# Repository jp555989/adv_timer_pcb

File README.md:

# adv_timer_pcb

This is a small project I made for one of my academic courses, I picked a task involving conversion from a THT based PCB to SMT based PCB, for the board I used in conversion I picked
an advanced impulse timer, the THT board can be seen here:
https://ep.com.pl/projekty/projekty-ep/15648-zaawansowany-licznik-impulsow

I didn't change mounting technology of components like microcontroller for the sake of comfort since it'd be easier to dismount it in case of any issues or to reprogram it.

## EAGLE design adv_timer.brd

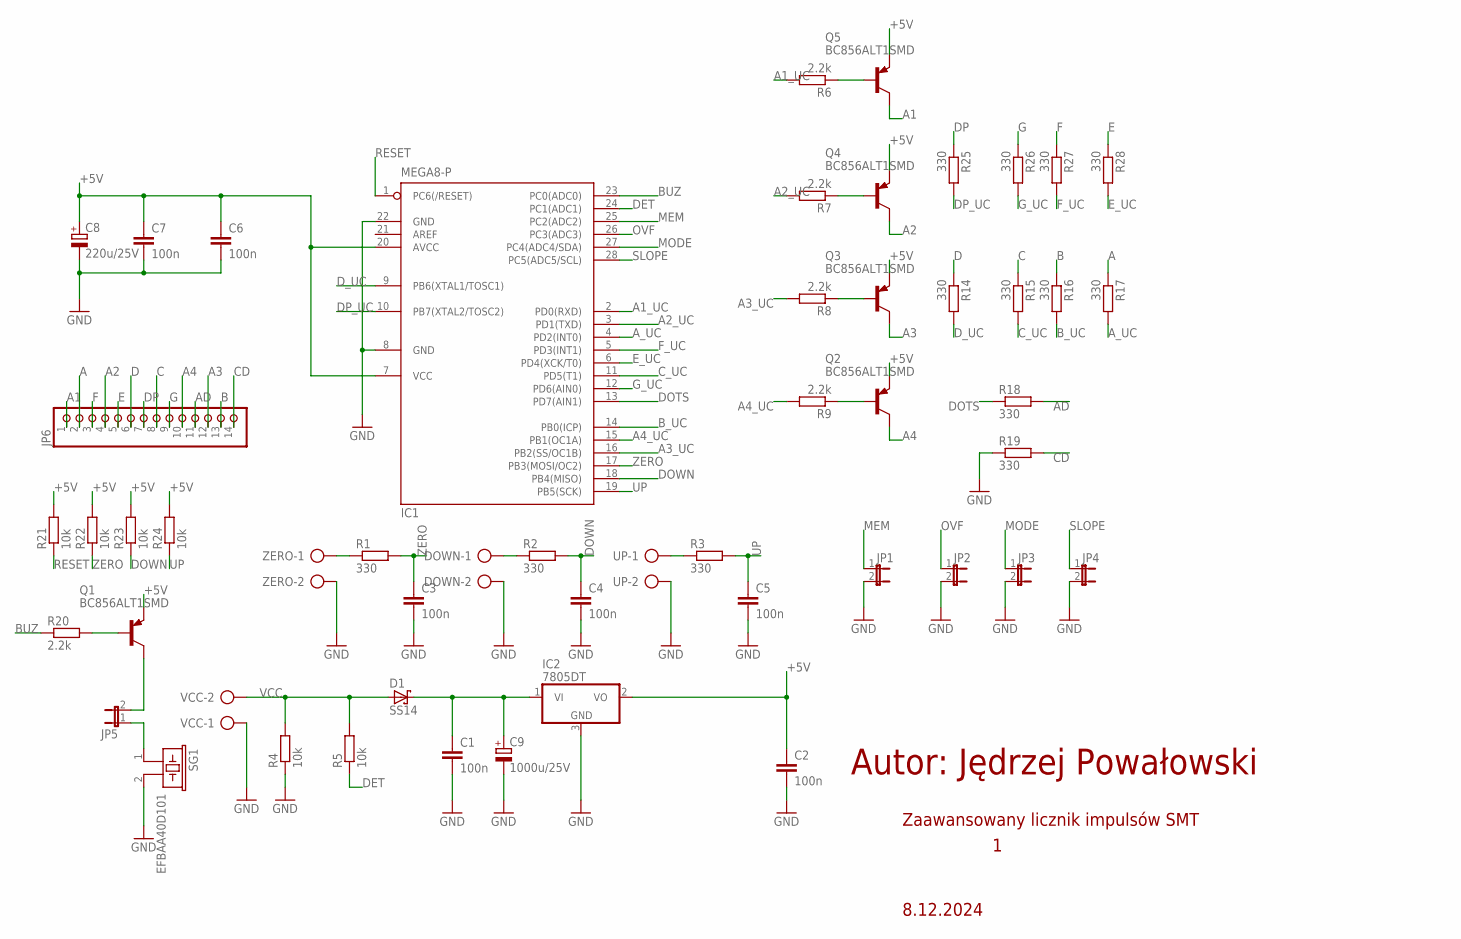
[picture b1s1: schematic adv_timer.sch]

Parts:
C1, C2, C3, C4, C5, C6, C7: 100n; C1210K
C8: 220u/25V; 153CLV-0810
C9: 1000u/25V; 153CLV-0810
D1: SS14; DO-214AC
DOWN: AK300/2
IC1: MEGA8-P; DIL28-3
IC2: 7805DT; TO252
JP1, JP2, JP3, JP4, JP5: JP1E; JP1
JP6: PINHD-1X14/90; 1X14/90
Q1, Q2, Q3, Q4, Q5: BC856ALT1SMD; SOT23-BEC
R1, R2, R3: 330; M1206
R4, R5: 10k; M1206
R6, R7, R8, R9, R20: 2.2k; R0805
R14, R15, R16, R17, R18, R19, R25, R26, R27, R28: 330; R0805
R21, R22, R23, R24: 10k; R0805
SG1: EFBAA40D101
UP: AK300/2
VCC: AK300/2
ZERO: AK300/2

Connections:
+5V: C2.1, C6.1, C7.1, C8.+, IC1.7 (VCC), IC1.20 (AVCC), IC2.2 (VO), Q1.E, Q2.E, Q3.E, Q4.E, Q5.E, R21.2, R22.2, R23.2, R24.2
A: JP6.2, R17.1
A1: JP6.1, Q5.C
A1_UC: IC1.2 (PD0(RXD)), R6.2
A2: JP6.4, Q4.C
A2_UC: IC1.3 (PD1(TXD)), R7.2
A3: JP6.12, Q3.C
A3_UC: IC1.16 (PB2(SS/OC1B)), R8.2
A4: JP6.10, Q2.C
A4_UC: IC1.15 (PB1(OC1A)), R9.2
AD: JP6.11, R18.2
A_UC: IC1.4 (PD2(INT0)), R17.2
B: JP6.13, R16.1
BUZ: IC1.23 (PC0(ADC0)), R20.1
B_UC: IC1.14 (PB0(ICP)), R16.2
C: JP6.8, R15.1
CD: JP6.14, R19.2
C_UC: IC1.11 (PD5(T1)), R15.2
D: JP6.6, R14.1
DET: IC1.24 (PC1(ADC1)), R5.1
DOTS: IC1.13 (PD7(AIN1)), R18.1
DOWN: C4.1, IC1.18 (PB4(MISO)), R2.2, R23.1
DP: JP6.7, R25.1
DP_UC: IC1.10 (PB7(XTAL2/TOSC2)), R25.2
D_UC: IC1.9 (PB6(XTAL1/TOSC1)), R14.2
E: JP6.5, R28.1
E_UC: IC1.6 (PD4(XCK/T0)), R28.2
F: JP6.3, R27.1
F_UC: IC1.5 (PD3(INT1)), R27.2
G: JP6.9, R26.1
GND: C1.2, C2.2, C3.2, C4.2, C5.2, C6.2, C7.2, C8.-, C9.-, DOWN.2, IC1.8 (GND), IC1.22 (GND), IC2.3 (GND), JP1.2, JP2.2, JP3.2, JP4.2, R4.1, R19.1, SG1.2, UP.2, VCC.1, ZERO.2
G_UC: IC1.12 (PD6(AIN0)), R26.2
MEM: IC1.25 (PC2(ADC2)), JP1.1
MODE: IC1.27 (PC4(ADC4/SDA)), JP3.1
unnamed: Q2.B, R9.1
unnamed: Q3.B, R8.1
unnamed: Q4.B, R7.1
unnamed: Q1.B, R20.2
unnamed: Q5.B, R6.1
unnamed: C1.1, C9.+, D1.K, IC2.1 (VI)
unnamed: JP5.2, Q1.C
unnamed: JP5.1, SG1.1
unnamed: R1.1, ZERO.1
unnamed: DOWN.1, R2.1
unnamed: R3.1, UP.1
OVF: IC1.26 (PC3(ADC3)), JP2.1
RESET: IC1.1 (PC6(/RESET)), R21.1
SLOPE: IC1.28 (PC5(ADC5/SCL)), JP4.1
UP: C5.1, IC1.19 (PB5(SCK)), R3.2, R24.1
VCC: D1.A, R4.2, R5.2, VCC.2
ZERO: C3.1, IC1.17 (PB3(MOSI/OC2)), R1.2, R22.1

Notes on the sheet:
Autor: Jędrzej Powałowski
8.12.2024
Zaawansowany licznik impulsów SMT

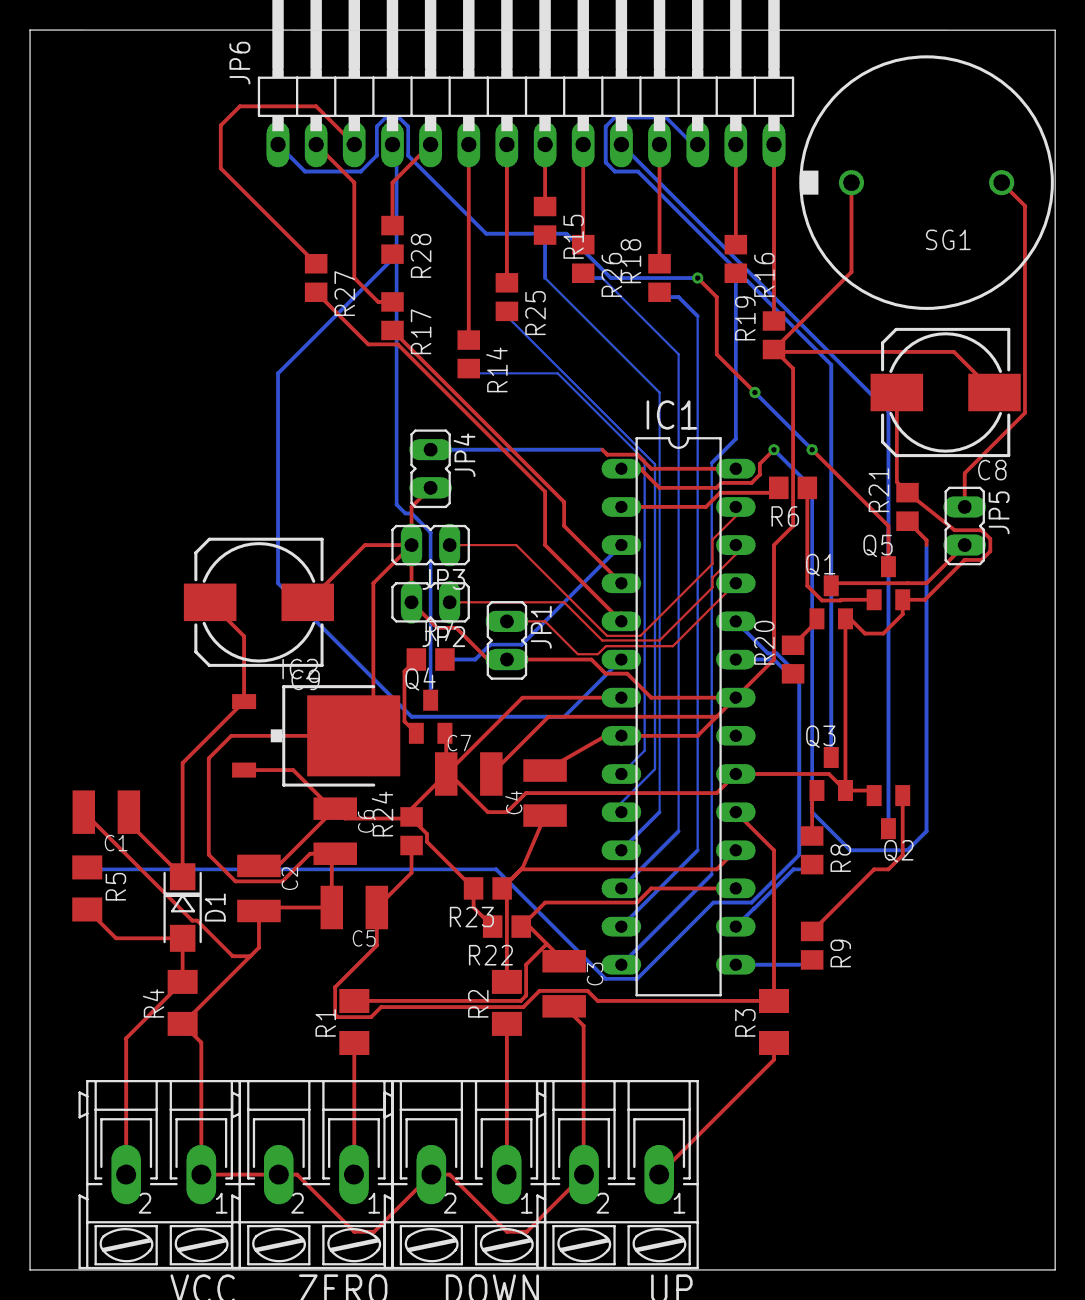
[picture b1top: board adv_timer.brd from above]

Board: 2 copper layers, 68.2 x 82.5 mm, 52 parts (0 on the bottom side), 51 nets.
